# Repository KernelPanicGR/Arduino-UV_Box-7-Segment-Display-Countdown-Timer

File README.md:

# Arduino UV Box Countdown Timer 
Multiplexing 4-Digit 7-Segment Display<br/>
Easy change between Common Cathode or Common Anode Displays<br/>
Stores values into the EEPROM <br/>
max. countdown time 99:59 [min:sec]<br/>
Video https://vimeo.com/608781008<br/>

To change the countdown time, press the UP & DOWN buttons together.<br/>
With the UP or DOWN buttons put the time you want in minutes and press START/STOP which now works as SET. <br/>
Now change the seconds and press START/STOP again.<br/>
If other knowledge, repeat the previous steps, if you are ready press START/STOP to start the countdown.<br/>
If the time was different from the previous one Arduino had in EEPROM, the word Set will appear on the screen first,<br/>
the new time in EEPROM will be saved and then the reverse will start.

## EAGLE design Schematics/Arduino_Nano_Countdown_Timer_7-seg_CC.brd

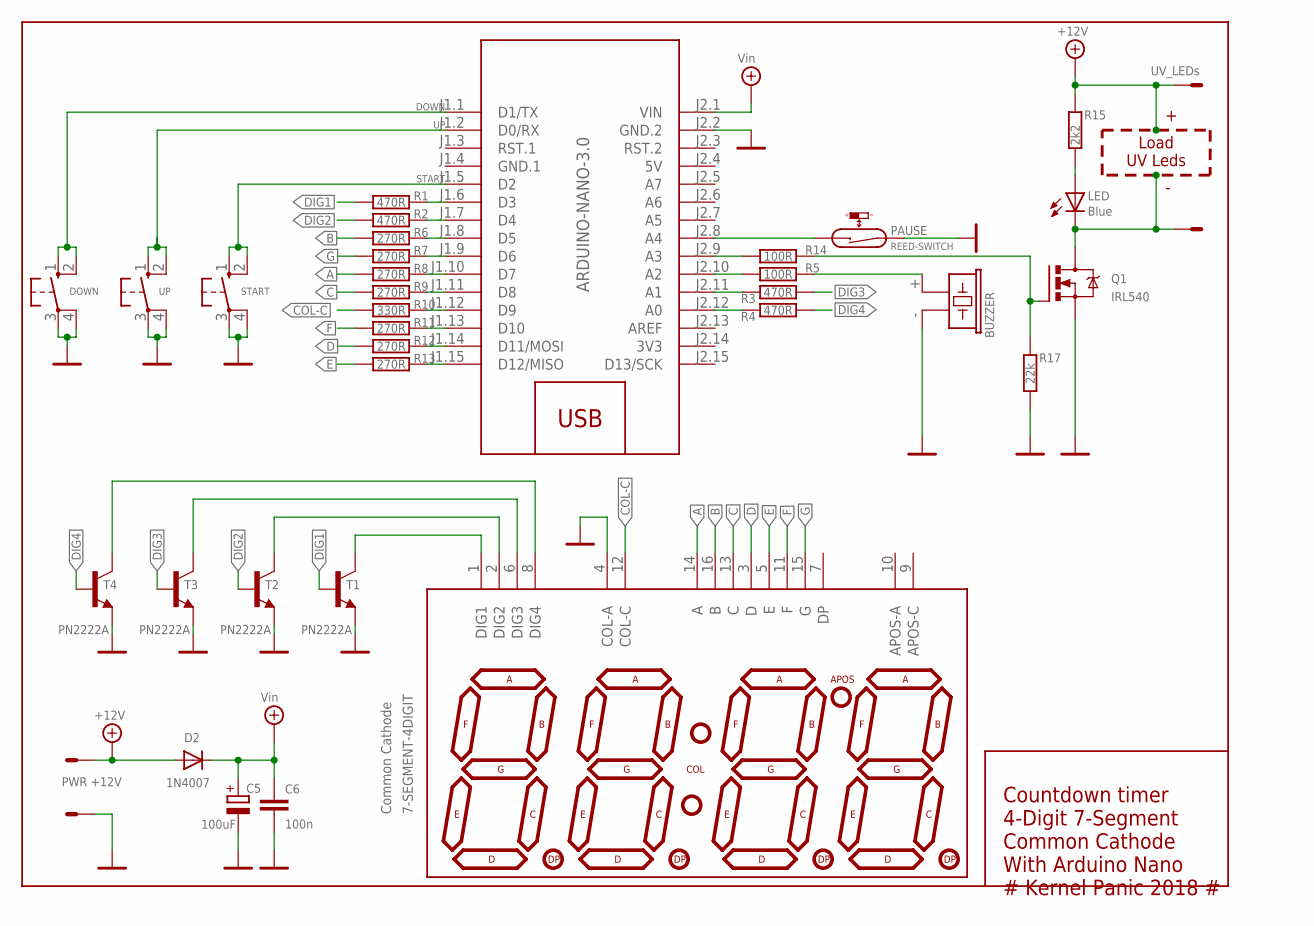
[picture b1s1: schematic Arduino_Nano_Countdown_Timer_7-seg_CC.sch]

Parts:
BUZZER: F/CM12P
C5: 100uF; E5-6.5
C6: 100n; C050-025X075
D2: 1N4007; DO41-10
DOWN: SWITCHE6K; DTE6K
LED: Blue; LED3MM
LED2: 7-SEGMENT-4DIGIT
LOAD: UV_LEDs; 22-23-2021
M2: ARDUINO-NANO-3.0
PAUSE: REED-SWITCH; 2PIN_HEADER
PWR: PWR +12V; 22-23-2021
Q1: IRL540; TO220BV
R1, R2, R3, R4: 470R; R0805
R5: 100R; R0805
R6, R7, R8, R9, R11, R12, R13: 270R; R0805
R10: 330R; R0805
R14: 100R; 0207/10-8
R15: 2k2; R0805
R17: 22k; R0805
START: SWITCHE6K; DTE6K
T1, T2, T3, T4: PN2222A; TO92-EBC-OVAL
UP: SWITCHE6K; DTE6K

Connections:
3V3: M2.J2.14 (3V3)
5V: M2.J2.4 (5V)
+12V: D2.A, LOAD.1, PWR.2, R15.1
A: LED2.14 (A), R8.1
B: LED2.16 (B), R6.1
BUZZER: BUZZER.+ (1), R5.1
C: LED2.13 (C), R9.1
COL-C: LED2.12 (COL-C), R10.1
D: LED2.3 (D), R12.1
DG1: LED2.1 (DIG1), T1.C
DG2: LED2.2 (DIG2), T2.C
DG3: LED2.6 (DIG3), T3.C
DG4: LED2.8 (DIG4), T4.C
DIG1: R1.1, T1.B
DIG2: R2.1, T2.B
DIG3: R3.1, T3.B
DIG4: R4.1, T4.B
DOWN: DOWN.1 (S), DOWN.2 (S), M2.J1.1 (D1/TX)
DP: M2.J1.12 (D9), R10.2
DRAIN: LED.K (C), LOAD.2, Q1.D
E: LED2.5 (E), R13.1
F: LED2.11 (F), R11.1
G: LED2.15 (G), R7.1
GATE: Q1.G, R14.2, R17.1
GND: BUZZER.- (2), C5.-, C6.2, DOWN.3, DOWN.4, LED2.4 (COL-A), M2.J2.2 (GND.2), PAUSE.2, PWR.1, Q1.S, R17.2, START.3, START.4, T1.E, T2.E, T3.E, T4.E, UP.3, UP.4
GND.1: M2.J1.4 (GND.1)
LED: LED.A, R15.2
unnamed: M2.J1.15 (D12/MISO), R13.2
unnamed: M2.J1.14 (D11/MOSI), R12.2
unnamed: M2.J2.10 (A2), R5.2
unnamed: M2.J2.9 (A3), R14.1
unnamed: M2.J1.13 (D10), R11.2
unnamed: M2.J1.6 (D3), R1.2
unnamed: M2.J2.11 (A1), R3.2
unnamed: M2.J1.7 (D4), R2.2
unnamed: M2.J2.8 (A4), PAUSE.1
unnamed: M2.J2.12 (A0), R4.2
unnamed: M2.J1.11 (D8), R9.2
unnamed: M2.J1.10 (D7), R8.2
unnamed: M2.J1.9 (D6), R7.2
unnamed: M2.J1.8 (D5), R6.2
START: M2.J1.5 (D2), START.1 (S), START.2 (S)
UP: M2.J1.2 (D0/RX), UP.1 (S), UP.2 (S)
VIN: C5.+, C6.1, D2.C, M2.J2.1 (VIN)

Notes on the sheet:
Load UV Leds
Countdown timer 4-Digit 7-Segment Common Cathode With Arduino Nano # Kernel Panic 2018 #
Common Cathode

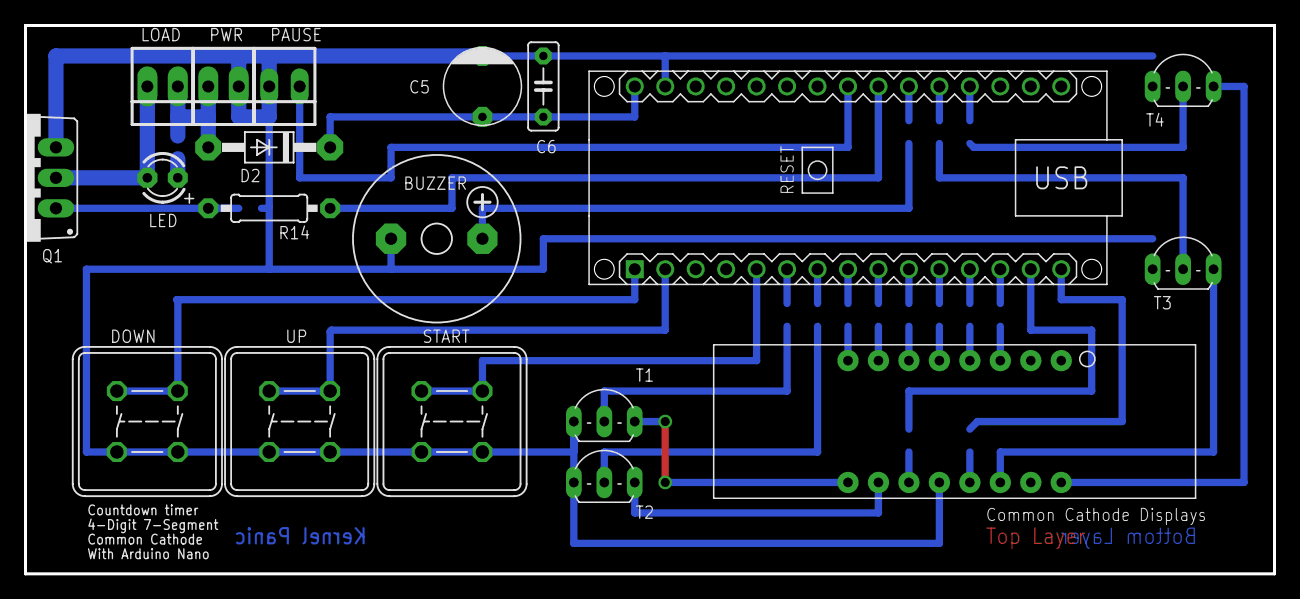
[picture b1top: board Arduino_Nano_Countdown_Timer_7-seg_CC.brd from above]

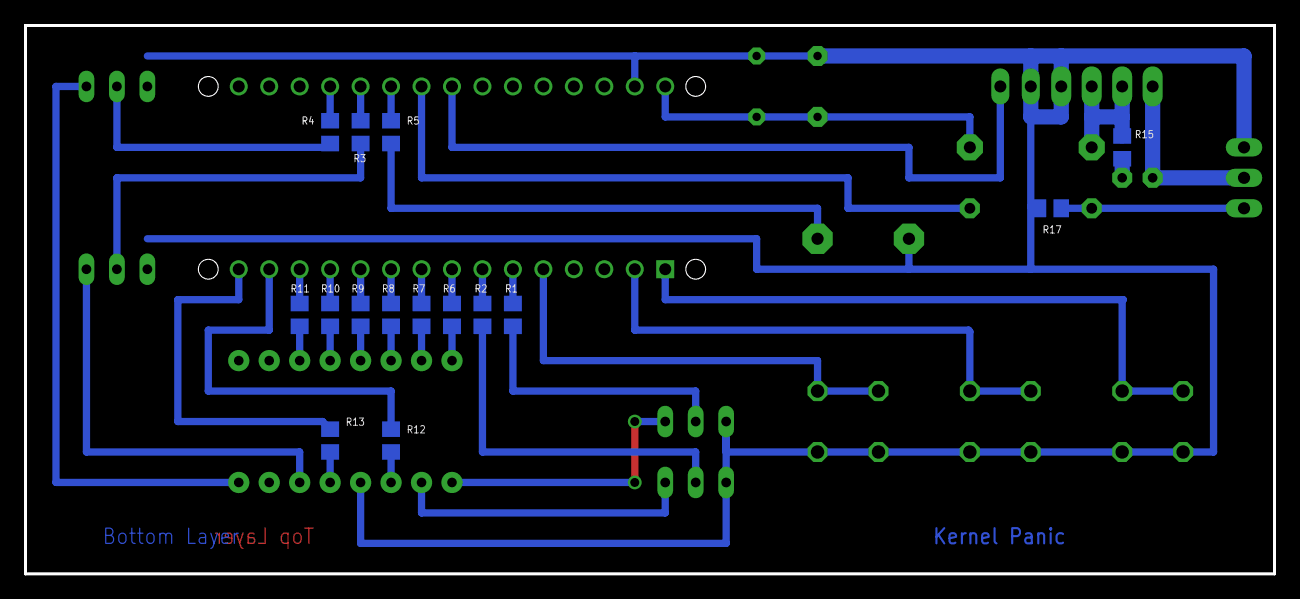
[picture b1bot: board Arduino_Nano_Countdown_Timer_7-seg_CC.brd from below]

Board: 2 copper layers, 104.1 x 45.7 mm, 34 parts (15 on the bottom side), 41 nets.

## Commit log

2021-09-09 Add files via upload
    Arduino Multiplexing 4-Digit 7-Segment Display Countdown Timer
    Select Common Cathode or Common Anode Displays
    max. countdown time 99:59 [min:sec]
2021-09-13 images
    images

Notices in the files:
parts and their libraries:
diy-modules: Released under the Creative Commons Attribution 4.0 International License: http://creativecommons.org/licenses/by/4.0
